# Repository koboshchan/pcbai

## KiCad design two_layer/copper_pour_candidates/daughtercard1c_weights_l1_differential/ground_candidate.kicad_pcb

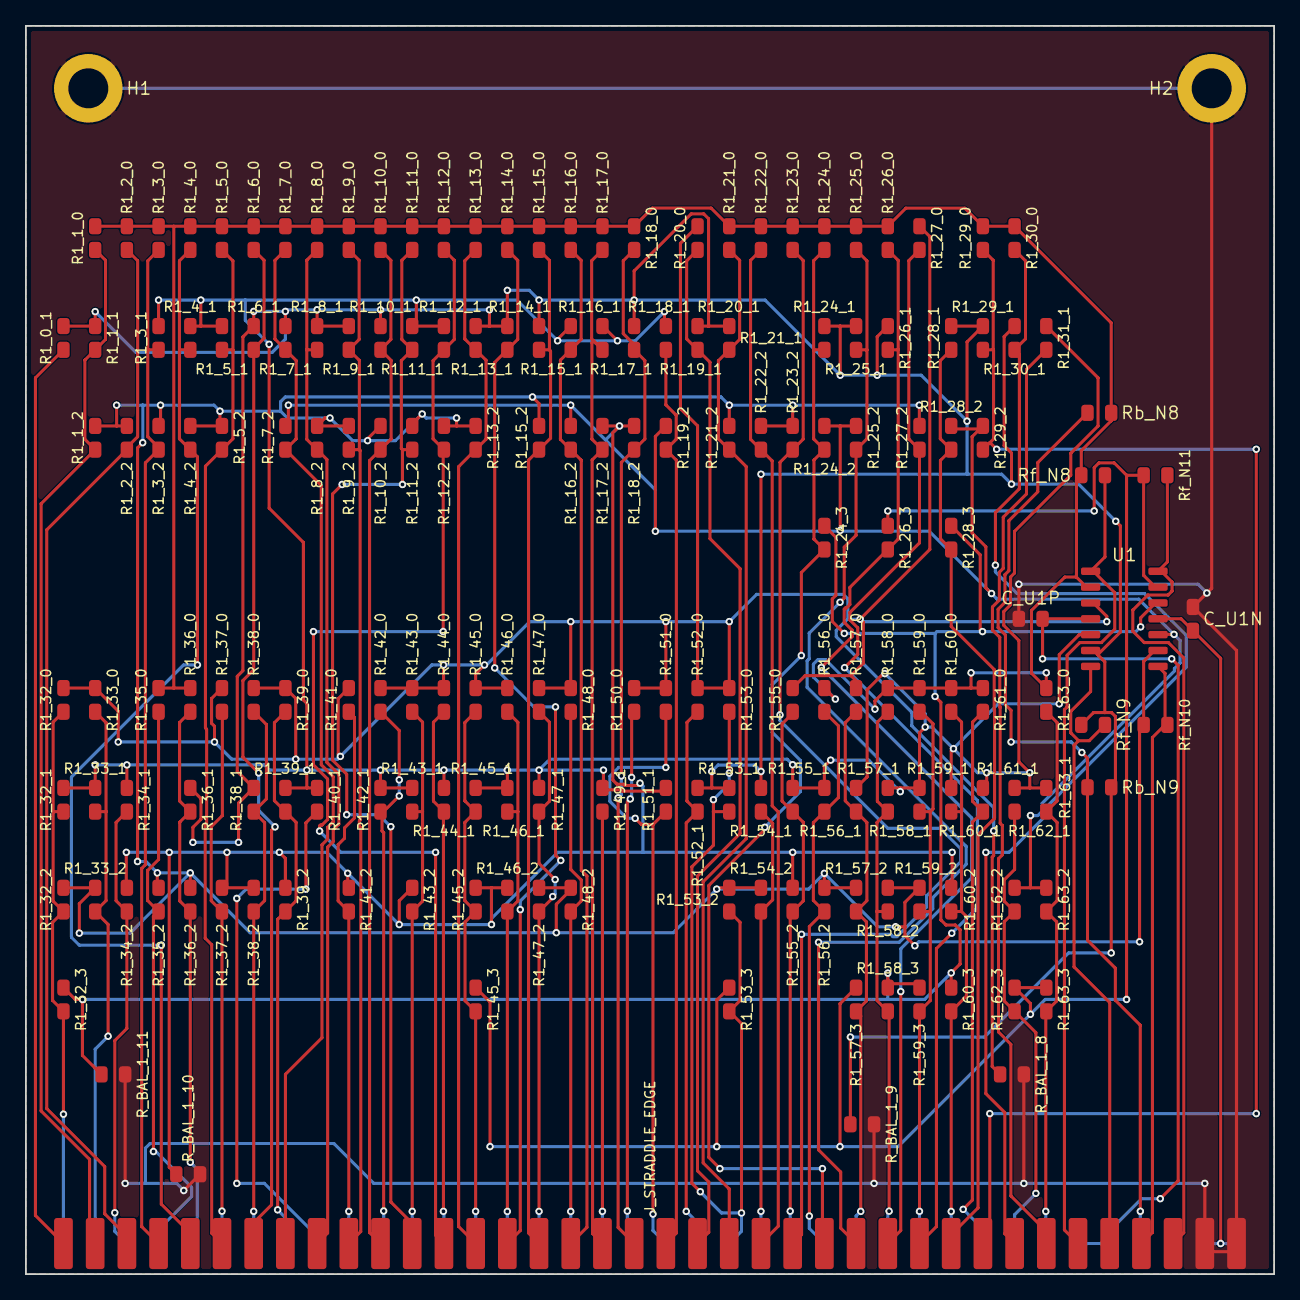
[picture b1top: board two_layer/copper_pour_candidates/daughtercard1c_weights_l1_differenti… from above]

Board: 2 copper layers, 100.0 x 100.0 mm, 187 parts (0 on the bottom side), 80 nets.

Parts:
C_U1N, C_U1P: 0.1uF; C_0805_2012Metric
H1, H2: MountingHole; MountingHole_3.2mm_M3_Pad
J_STRADDLE_EDGE: PinHeader_2x38_Straddle; PinHeader_2x38_Straddle_P2.54mm
R1_0_1: 51k; R_0805_2012Metric
R1_1_0, R1_4_0, R1_11_1, R1_13_1, R1_23_2, R1_28_3, R1_43_1, R1_45_0: 180k; R_0805_2012Metric
R1_1_1: 33k; R_0805_2012Metric
R1_1_2, R1_4_1: 43k; R_0805_2012Metric
R1_2_0, R1_22_2, R1_26_1, R1_28_2, R1_33_1, R1_37_0, R1_37_2, R1_39_2, R1_44_0, R1_44_1, R1_45_1, R1_46_1, R1_48_2, R1_49_1, R1_59_2: 270k; R_0805_2012Metric
R1_2_2, R1_3_1, R1_18_2, R1_56_0: 62k; R_0805_2012Metric
R1_3_0, R1_36_2: 1M; R_0805_2012Metric
R1_3_2, R1_18_0, R1_22_0: 120k; R_0805_2012Metric
R1_4_2, R1_14_1, R1_17_0, R1_18_1, R1_34_1, R1_63_1: 160k; R_0805_2012Metric
R1_5_0, R1_9_1, R1_11_0, R1_47_2, R1_59_0: 360k; R_0805_2012Metric
R1_5_1, R1_8_0, R1_19_2: 75k; R_0805_2012Metric
R1_5_2, R1_10_1, R1_21_1, R1_28_1, R1_39_0, R1_41_0, R1_45_3, R1_63_0: 240k; R_0805_2012Metric
R1_6_0, R1_12_2, R1_19_1, R1_33_2, R1_57_2: 330k; R_0805_2012Metric
R1_6_1, R1_11_2, R1_15_1, R1_16_0, R1_32_0, R1_56_1, R1_60_3, R1_62_1: 110k; R_0805_2012Metric
R1_7_0, R1_16_2, R1_17_2, R1_32_2: 47k; R_0805_2012Metric
R1_7_1, R1_8_2, R1_47_1: 39k; R_0805_2012Metric
R1_7_2: 27k; R_0805_2012Metric
R1_8_1, R1_10_2, R1_16_1, R1_32_1, R1_38_0: 91k; R_0805_2012Metric
R1_9_0, R1_52_0, R1_53_0, R1_53_2: 620k; R_0805_2012Metric
R1_9_2, R1_56_2: 100k; R_0805_2012Metric
R1_10_0, R1_13_0, R1_17_1, R1_50_0, R1_51_0, R1_58_1, R1_58_2: 220k; R_0805_2012Metric
R1_12_0, R1_33_0, R1_46_2: 430k; R_0805_2012Metric
R1_12_1, R1_42_1, R1_43_0, R1_53_3, R1_57_0, R1_59_3, R1_61_0: 300k; R_0805_2012Metric
R1_13_2, R1_26_0, R1_43_2, R1_47_0, R1_58_3, R1_63_3: 560k; R_0805_2012Metric
R1_14_0, R1_38_1, R1_38_2, R1_60_0: 510k; R_0805_2012Metric
R1_15_0, R1_40_1, R1_61_1: 68k; R_0805_2012Metric
R1_15_2: 82k; R_0805_2012Metric
R1_20_0, R1_25_0, R1_27_0, R1_42_0, R1_60_1: 470k; R_0805_2012Metric
R1_20_1, R1_35_0, R1_41_2, R1_59_1: 390k; R_0805_2012Metric
R1_21_0, R1_23_0, R1_24_1, R1_30_1, R1_39_1, R1_57_1: 130k; R_0805_2012Metric
R1_21_2, R1_32_3, R1_34_2: 910k; R_0805_2012Metric
R1_24_0, R1_30_0, R1_54_2, R1_62_2: 200k; R_0805_2012Metric
R1_24_2, R1_55_1: 56k; R_0805_2012Metric
R1_24_3, R1_25_2, R1_35_2, R1_36_0, R1_51_1, R1_52_1: 750k; R_0805_2012Metric
R1_25_1, R1_29_1, R1_46_0, R1_57_3, R1_62_3: 150k; R_0805_2012Metric
R1_26_3: 2.2M; R_0805_2012Metric
R1_27_2, R1_53_1, R1_54_1, R1_60_2: 820k; R_0805_2012Metric
R1_29_0, R1_55_0: 1.2M; R_0805_2012Metric
R1_29_2, R1_55_2: 1.3M; R_0805_2012Metric
R1_31_1: 3M; R_0805_2012Metric
R1_36_1, R1_48_0: 1.1M; R_0805_2012Metric
R1_45_2: 2M; R_0805_2012Metric
R1_58_0: 680k; R_0805_2012Metric
R1_63_2: 36k; R_0805_2012Metric
R_BAL_1_8: 8.66k; R_0805_2012Metric
R_BAL_1_9: 18.2k; R_0805_2012Metric
R_BAL_1_10: 35.7k; R_0805_2012Metric
R_BAL_1_11: 90.9k; R_0805_2012Metric
Rb_N8: 820k; R_0805_2012Metric
Rb_N9: 270k; R_0805_2012Metric
Rf_N8, Rf_N9, Rf_N10, Rf_N11: 100k; R_0805_2012Metric
U1: TL074; SOIC-14_3.9x8.7mm_P1.27mm

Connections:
+5V_REF: J_STRADDLE_EDGE.B35, Rb_N8.1, Rb_N9.1
+15V: C_U1P.2, J_STRADDLE_EDGE.B33, J_STRADDLE_EDGE.B34, U1.4
-15V: C_U1N.1, J_STRADDLE_EDGE.B37, J_STRADDLE_EDGE.B38, U1.11
GND: C_U1N.2, C_U1P.1, H1.1, H2.1, J_STRADDLE_EDGE.A37, J_STRADDLE_EDGE.A38, R_BAL_1_8.2, R_BAL_1_9.2, R_BAL_1_10.2, R_BAL_1_11.2
INV_N8: R1_1_0.2, R1_2_0.2, R1_3_0.2, R1_4_0.2, R1_5_0.2, R1_6_0.2, R1_7_0.2, R1_8_0.2, R1_9_0.2, R1_10_0.2, R1_11_0.2, R1_12_0.2, R1_13_0.2, R1_14_0.2, R1_15_0.2, R1_16_0.2, R1_17_0.2, R1_18_0.2, R1_21_0.2, R1_22_0.2, R1_23_0.2, R1_24_0.2, R1_25_0.2, R1_26_0.2, R1_29_0.2, R1_30_0.2, R1_35_0.2, R1_36_0.2, R1_56_0.2, R1_58_0.2, R1_59_0.2, R1_60_0.2, R1_61_0.2, R1_63_0.2, Rb_N8.2, Rf_N8.1, U1.2
INV_N9: R1_0_1.2, R1_1_1.2, R1_6_1.2, R1_7_1.2, R1_8_1.2, R1_9_1.2, R1_10_1.2, R1_13_1.2, R1_14_1.2, R1_15_1.2, R1_18_1.2, R1_20_1.2, R1_21_1.2, R1_24_1.2, R1_25_1.2, R1_26_1.2, R1_28_1.2, R1_29_1.2, R1_30_1.2, R1_36_1.2, R1_38_1.2, R1_52_1.2, R1_53_1.2, R1_54_1.2, R_BAL_1_9.1, Rb_N9.2, Rf_N9.1, U1.6
INV_N10: R1_1_2.2, R1_2_2.2, R1_3_2.2, R1_4_2.2, R1_5_2.2, R1_8_2.2, R1_9_2.2, R1_10_2.2, R1_11_2.2, R1_12_2.2, R1_13_2.2, R1_15_2.2, R1_21_2.2, R1_22_2.2, R1_23_2.2, R1_27_2.2, R1_32_2.2, R1_33_2.2, R1_35_2.2, R1_36_2.2, R1_47_2.2, R1_48_2.2, R1_53_2.2, R1_54_2.2, R1_56_2.2, R1_57_2.2, R1_58_2.2, R1_59_2.2, Rf_N10.1, U1.9
INV_N11: R1_26_3.2, R1_45_3.2, R1_53_3.2, R1_57_3.2, R1_62_3.2, R1_63_3.2, Rf_N11.1, U1.13
IN_0: J_STRADDLE_EDGE.A1, R1_0_1.1
IN_1: J_STRADDLE_EDGE.A2, R1_1_0.1, R1_1_1.1, R1_1_2.1
IN_2: J_STRADDLE_EDGE.A3, R1_2_0.1, R1_2_2.1
IN_3: J_STRADDLE_EDGE.A4, R1_3_0.1, R1_3_1.1, R1_3_2.1
IN_4: J_STRADDLE_EDGE.A5, R1_4_0.1, R1_4_1.1, R1_4_2.1
IN_5: J_STRADDLE_EDGE.A6, R1_5_0.1, R1_5_1.1, R1_5_2.1
IN_6: J_STRADDLE_EDGE.A7, R1_6_0.1, R1_6_1.1
IN_7: J_STRADDLE_EDGE.A8, R1_7_0.1, R1_7_1.1, R1_7_2.1
IN_8: J_STRADDLE_EDGE.A9, R1_8_0.1, R1_8_1.1, R1_8_2.1
IN_9: J_STRADDLE_EDGE.A10, R1_9_0.1, R1_9_1.1, R1_9_2.1
IN_10: J_STRADDLE_EDGE.A11, R1_10_0.1, R1_10_1.1, R1_10_2.1
IN_11: J_STRADDLE_EDGE.A12, R1_11_0.1, R1_11_1.1, R1_11_2.1
IN_12: J_STRADDLE_EDGE.A13, R1_12_0.1, R1_12_1.1, R1_12_2.1
IN_13: J_STRADDLE_EDGE.A14, R1_13_0.1, R1_13_1.1, R1_13_2.1
IN_14: J_STRADDLE_EDGE.A15, R1_14_0.1, R1_14_1.1
IN_15: J_STRADDLE_EDGE.A16, R1_15_0.1, R1_15_1.1, R1_15_2.1
IN_16: J_STRADDLE_EDGE.A17, R1_16_0.1, R1_16_1.1, R1_16_2.1
IN_17: J_STRADDLE_EDGE.A18, R1_17_0.1, R1_17_1.1, R1_17_2.1
IN_18: J_STRADDLE_EDGE.A19, R1_18_0.1, R1_18_1.1, R1_18_2.1
IN_19: J_STRADDLE_EDGE.A20, R1_19_1.1, R1_19_2.1
IN_20: J_STRADDLE_EDGE.A21, R1_20_0.1, R1_20_1.1
IN_21: J_STRADDLE_EDGE.A22, R1_21_0.1, R1_21_1.1, R1_21_2.1
IN_22: J_STRADDLE_EDGE.A23, R1_22_0.1, R1_22_2.1
IN_23: J_STRADDLE_EDGE.A24, R1_23_0.1, R1_23_2.1
IN_24: J_STRADDLE_EDGE.A25, R1_24_0.1, R1_24_1.1, R1_24_2.1, R1_24_3.1
IN_25: J_STRADDLE_EDGE.A26, R1_25_0.1, R1_25_1.1, R1_25_2.1
IN_26: J_STRADDLE_EDGE.A27, R1_26_0.1, R1_26_1.1, R1_26_3.1
IN_27: J_STRADDLE_EDGE.A28, R1_27_0.1, R1_27_2.1
IN_28: J_STRADDLE_EDGE.A29, R1_28_1.1, R1_28_2.1, R1_28_3.1
IN_29: J_STRADDLE_EDGE.A30, R1_29_0.1, R1_29_1.1, R1_29_2.1
IN_30: J_STRADDLE_EDGE.A31, R1_30_0.1, R1_30_1.1
IN_31: J_STRADDLE_EDGE.A32, R1_31_1.1
IN_32: J_STRADDLE_EDGE.B1, R1_32_0.1, R1_32_1.1, R1_32_2.1, R1_32_3.1
IN_33: J_STRADDLE_EDGE.B2, R1_33_0.1, R1_33_1.1, R1_33_2.1
IN_34: J_STRADDLE_EDGE.B3, R1_34_1.1, R1_34_2.1
IN_35: J_STRADDLE_EDGE.B4, R1_35_0.1, R1_35_2.1
IN_36: J_STRADDLE_EDGE.B5, R1_36_0.1, R1_36_1.1, R1_36_2.1
IN_37: J_STRADDLE_EDGE.B6, R1_37_0.1, R1_37_2.1
IN_38: J_STRADDLE_EDGE.B7, R1_38_0.1, R1_38_1.1, R1_38_2.1
IN_39: J_STRADDLE_EDGE.B8, R1_39_0.1, R1_39_1.1, R1_39_2.1
IN_40: J_STRADDLE_EDGE.B9, R1_40_1.1
IN_41: J_STRADDLE_EDGE.B10, R1_41_0.1, R1_41_2.1
IN_42: J_STRADDLE_EDGE.B11, R1_42_0.1, R1_42_1.1
IN_43: J_STRADDLE_EDGE.B12, R1_43_0.1, R1_43_1.1, R1_43_2.1
IN_44: J_STRADDLE_EDGE.B13, R1_44_0.1, R1_44_1.1
IN_45: J_STRADDLE_EDGE.B14, R1_45_0.1, R1_45_1.1, R1_45_2.1, R1_45_3.1
IN_46: J_STRADDLE_EDGE.B15, R1_46_0.1, R1_46_1.1, R1_46_2.1
IN_47: J_STRADDLE_EDGE.B16, R1_47_0.1, R1_47_1.1, R1_47_2.1
IN_48: J_STRADDLE_EDGE.B17, R1_48_0.1, R1_48_2.1
IN_49: J_STRADDLE_EDGE.B18, R1_49_1.1
IN_50: J_STRADDLE_EDGE.B19, R1_50_0.1
IN_51: J_STRADDLE_EDGE.B20, R1_51_0.1, R1_51_1.1
IN_52: J_STRADDLE_EDGE.B21, R1_52_0.1, R1_52_1.1
IN_53: J_STRADDLE_EDGE.B22, R1_53_0.1, R1_53_1.1, R1_53_2.1, R1_53_3.1
IN_54: J_STRADDLE_EDGE.B23, R1_54_1.1, R1_54_2.1
IN_55: J_STRADDLE_EDGE.B24, R1_55_0.1, R1_55_1.1, R1_55_2.1
IN_56: J_STRADDLE_EDGE.B25, R1_56_0.1, R1_56_1.1, R1_56_2.1
IN_57: J_STRADDLE_EDGE.B26, R1_57_0.1, R1_57_1.1, R1_57_2.1, R1_57_3.1
IN_58: J_STRADDLE_EDGE.B27, R1_58_0.1, R1_58_1.1, R1_58_2.1, R1_58_3.1
IN_59: J_STRADDLE_EDGE.B28, R1_59_0.1, R1_59_1.1, R1_59_2.1, R1_59_3.1
IN_60: J_STRADDLE_EDGE.B29, R1_60_0.1, R1_60_1.1, R1_60_2.1, R1_60_3.1
IN_61: J_STRADDLE_EDGE.B30, R1_61_0.1, R1_61_1.1
IN_62: J_STRADDLE_EDGE.B31, R1_62_1.1, R1_62_2.1, R1_62_3.1
IN_63: J_STRADDLE_EDGE.B32, R1_63_0.1, R1_63_1.1, R1_63_2.1, R1_63_3.1
POS_N8: R1_20_0.2, R1_27_0.2, R1_32_0.2, R1_33_0.2, R1_37_0.2, R1_38_0.2, R1_39_0.2, R1_41_0.2, R1_42_0.2, R1_43_0.2, R1_44_0.2, R1_45_0.2, R1_46_0.2, R1_47_0.2, R1_48_0.2, R1_50_0.2, R1_51_0.2, R1_52_0.2, R1_53_0.2, R1_55_0.2, R1_57_0.2, R_BAL_1_8.1, U1.3
POS_N9: R1_3_1.2, R1_4_1.2, R1_5_1.2, R1_11_1.2, R1_12_1.2, R1_16_1.2, R1_17_1.2, R1_19_1.2, R1_31_1.2, R1_32_1.2, R1_33_1.2, R1_34_1.2, R1_39_1.2, R1_40_1.2, R1_42_1.2, R1_43_1.2, R1_44_1.2, R1_45_1.2, R1_46_1.2, R1_47_1.2, R1_49_1.2, R1_51_1.2, R1_55_1.2, R1_56_1.2, R1_57_1.2, R1_58_1.2, R1_59_1.2, R1_60_1.2, R1_61_1.2, R1_62_1.2, R1_63_1.2, U1.5
POS_N10: R1_7_2.2, R1_16_2.2, R1_17_2.2, R1_18_2.2, R1_19_2.2, R1_24_2.2, R1_25_2.2, R1_28_2.2, R1_29_2.2, R1_34_2.2, R1_37_2.2, R1_38_2.2, R1_39_2.2, R1_41_2.2, R1_43_2.2, R1_45_2.2, R1_46_2.2, R1_55_2.2, R1_60_2.2, R1_62_2.2, R1_63_2.2, R_BAL_1_10.1, U1.10
POS_N11: R1_24_3.2, R1_28_3.2, R1_32_3.2, R1_58_3.2, R1_59_3.2, R1_60_3.2, R_BAL_1_11.1, U1.12
V_SUM_8: J_STRADDLE_EDGE.A33, Rf_N8.2, U1.1
V_SUM_9: J_STRADDLE_EDGE.A34, Rf_N9.2, U1.7
V_SUM_10: J_STRADDLE_EDGE.A35, Rf_N10.2, U1.8
V_SUM_11: J_STRADDLE_EDGE.A36, Rf_N11.2, U1.14

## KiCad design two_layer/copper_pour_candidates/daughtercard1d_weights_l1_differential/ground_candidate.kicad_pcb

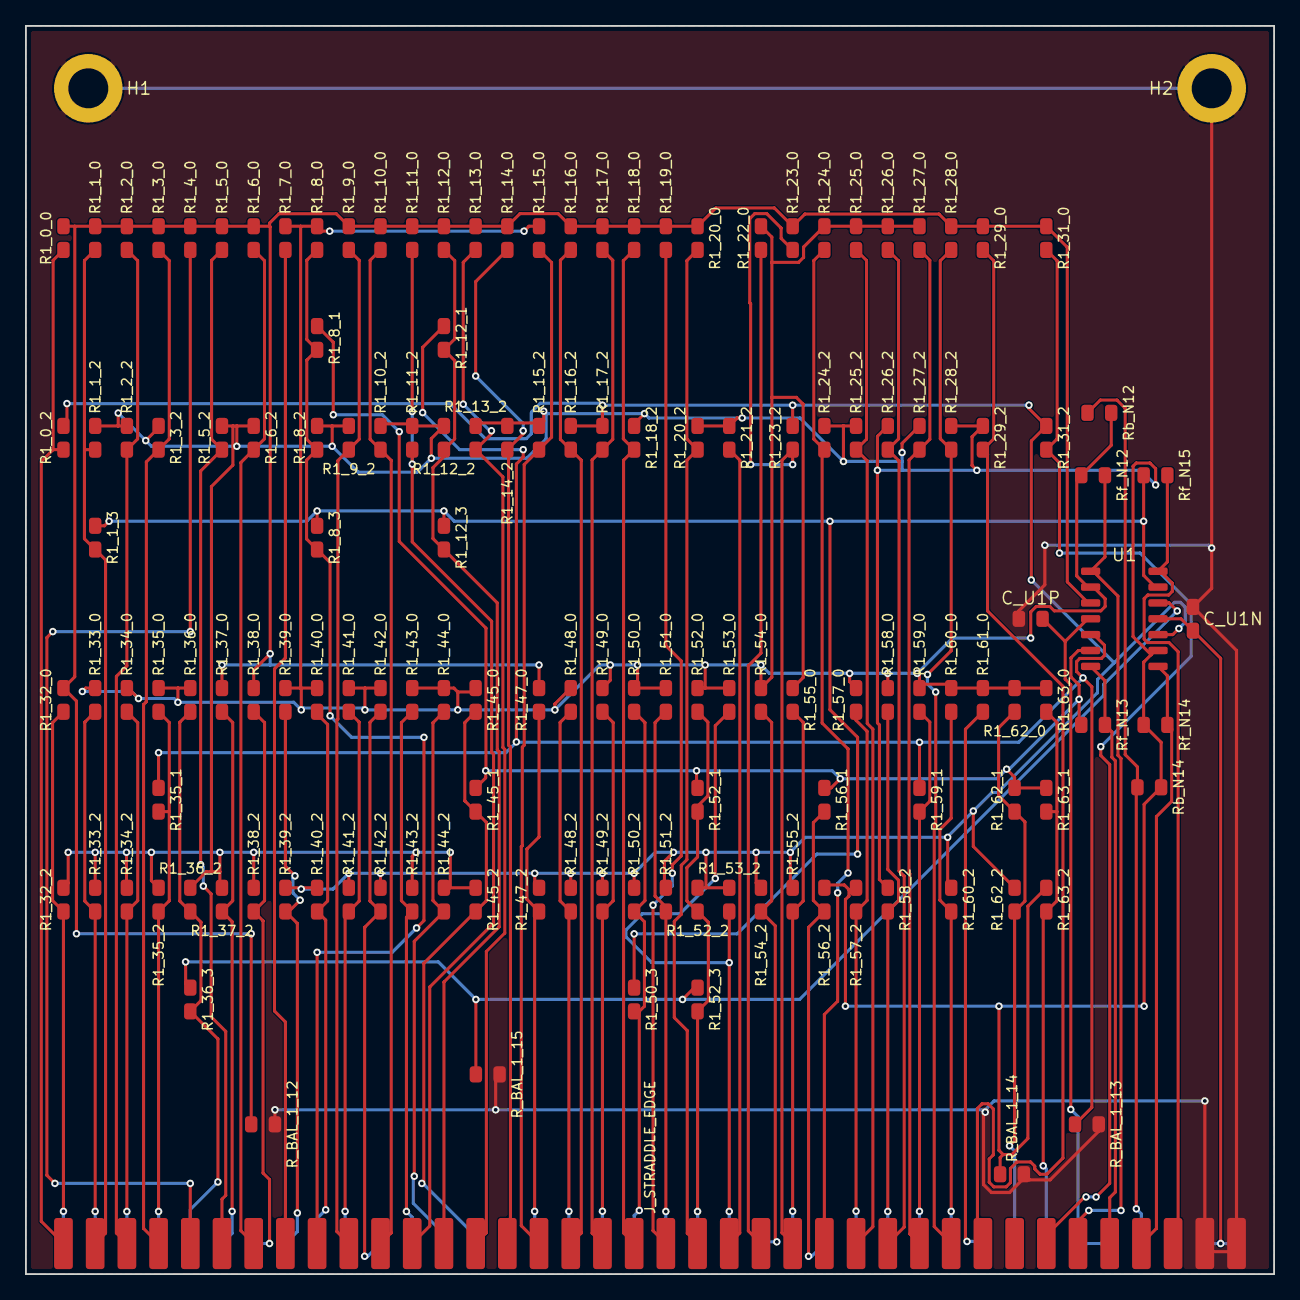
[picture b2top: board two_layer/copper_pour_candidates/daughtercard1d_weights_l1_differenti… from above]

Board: 2 copper layers, 100.0 x 100.0 mm, 147 parts (0 on the bottom side), 78 nets.

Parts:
C_U1N, C_U1P: 0.1uF; C_0805_2012Metric
H1, H2: MountingHole; MountingHole_3.2mm_M3_Pad
J_STRADDLE_EDGE: PinHeader_2x38_Straddle; PinHeader_2x38_Straddle_P2.54mm
R1_0_0: 43k; R_0805_2012Metric
R1_0_2, R1_31_2: 39k; R_0805_2012Metric
R1_1_0, R1_3_0, R1_5_2, R1_51_0, R1_56_1, R1_62_0, R1_62_1: 200k; R_0805_2012Metric
R1_1_2, R1_39_2: 91k; R_0805_2012Metric
R1_1_3, R1_12_3, R1_15_0, R1_17_2, R1_24_0, R1_34_0, R1_38_0: 220k; R_0805_2012Metric
R1_2_0, R1_13_0, R1_25_0, R1_63_1: 390k; R_0805_2012Metric
R1_2_2, R1_47_2, R1_55_0, R1_63_0: 100k; R_0805_2012Metric
R1_3_2, R1_24_2, R1_26_2, R1_48_2, R1_52_0, R1_59_0: 150k; R_0805_2012Metric
R1_4_0, R1_10_0, R1_14_2, R1_34_2, R1_50_0: 300k; R_0805_2012Metric
R1_5_0, R1_7_0, R1_9_2, R1_11_0, R1_13_2, R1_32_0, R1_37_2, R1_42_2, R1_49_0: 270k; R_0805_2012Metric
R1_6_0, R1_12_1, R1_18_2: 750k; R_0805_2012Metric
R1_6_2, R1_20_0: 110k; R_0805_2012Metric
R1_8_0, R1_25_2, R1_33_2, R1_36_2, R1_36_3, R1_41_2, R1_52_3, R1_57_0, R1_58_0, R1_61_0, R1_63_2: 160k; R_0805_2012Metric
R1_8_1, R1_28_2, R1_37_0, R1_40_0, R1_44_0, R1_45_0, R1_58_2: 430k; R_0805_2012Metric
R1_8_2, R1_56_2: 36k; R_0805_2012Metric
R1_8_3, R1_35_0, R1_41_0, R1_45_1, R1_59_1, R1_60_2: 180k; R_0805_2012Metric
R1_9_0, R1_43_2: 910k; R_0805_2012Metric
R1_10_2, R1_12_0, R1_26_0, R1_27_0, R1_35_2: 360k; R_0805_2012Metric
R1_11_2, R1_14_0, R1_16_0, R1_29_0, R1_33_0, R1_36_0, R1_52_1, R1_62_2: 330k; R_0805_2012Metric
R1_12_2: 1.1M; R_0805_2012Metric
R1_15_2, R1_47_0, R1_53_0: 120k; R_0805_2012Metric
R1_16_2, R1_52_2, R1_54_0: 75k; R_0805_2012Metric
R1_17_0, R1_23_0: 510k; R_0805_2012Metric
R1_18_0: 1M; R_0805_2012Metric
R1_19_0, R1_35_1, R1_39_0, R1_48_0: 130k; R_0805_2012Metric
R1_20_2: 820k; R_0805_2012Metric
R1_21_2: 2M; R_0805_2012Metric
R1_22_0: 1.5M; R_0805_2012Metric
R1_23_2: 51k; R_0805_2012Metric
R1_27_2, R1_45_2: 1.3M; R_0805_2012Metric
R1_28_0, R1_44_2: 560k; R_0805_2012Metric
R1_29_2, R1_32_2, R1_42_0: 470k; R_0805_2012Metric
R1_31_0, R1_38_2, R1_50_3, R1_55_2: 240k; R_0805_2012Metric
R1_40_2: 680k; R_0805_2012Metric
R1_43_0: 2.2M; R_0805_2012Metric
R1_49_2, R1_54_2: 68k; R_0805_2012Metric
R1_50_2, R1_57_2: 82k; R_0805_2012Metric
R1_51_2, R1_53_2: 62k; R_0805_2012Metric
R1_60_0: 1.2M; R_0805_2012Metric
R_BAL_1_12: 15.4k; R_0805_2012Metric
R_BAL_1_13: 52.3k; R_0805_2012Metric
R_BAL_1_14: 113k; R_0805_2012Metric
R_BAL_1_15: 61.9k; R_0805_2012Metric
Rb_N12: 750k; R_0805_2012Metric
Rb_N14: 200k; R_0805_2012Metric
Rf_N12, Rf_N13, Rf_N14, Rf_N15: 100k; R_0805_2012Metric
U1: TL074; SOIC-14_3.9x8.7mm_P1.27mm

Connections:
+5V_REF: J_STRADDLE_EDGE.B35, Rb_N12.1, Rb_N14.1
+15V: C_U1P.2, J_STRADDLE_EDGE.B33, J_STRADDLE_EDGE.B34, U1.4
-15V: C_U1N.1, J_STRADDLE_EDGE.B37, J_STRADDLE_EDGE.B38, U1.11
GND: C_U1N.2, C_U1P.1, H1.1, H2.1, J_STRADDLE_EDGE.A37, J_STRADDLE_EDGE.A38, R_BAL_1_12.2, R_BAL_1_13.2, R_BAL_1_14.2, R_BAL_1_15.2
INV_N12: R1_7_0.2, R1_8_0.2, R1_15_0.2, R1_22_0.2, R1_24_0.2, R1_25_0.2, R1_26_0.2, R1_27_0.2, R1_33_0.2, R1_34_0.2, R1_35_0.2, R1_36_0.2, R1_39_0.2, R1_40_0.2, R1_41_0.2, R1_42_0.2, R1_43_0.2, R1_44_0.2, R1_45_0.2, R1_48_0.2, R1_49_0.2, R1_50_0.2, R1_51_0.2, R1_52_0.2, R1_53_0.2, R1_54_0.2, R1_55_0.2, R1_57_0.2, R1_58_0.2, R1_59_0.2, R1_60_0.2, R1_61_0.2, R1_62_0.2, R1_63_0.2, Rb_N12.2, Rf_N12.1, U1.2
INV_N13: R1_8_1.2, R1_45_1.2, R1_52_1.2, R1_56_1.2, R1_62_1.2, R1_63_1.2, Rf_N13.1, U1.6
INV_N14: R1_1_2.2, R1_2_2.2, R1_3_2.2, R1_5_2.2, R1_6_2.2, R1_8_2.2, R1_9_2.2, R1_10_2.2, R1_11_2.2, R1_12_2.2, R1_13_2.2, R1_14_2.2, R1_15_2.2, R1_18_2.2, R1_20_2.2, R1_21_2.2, R1_24_2.2, R1_25_2.2, R1_26_2.2, R1_27_2.2, R1_28_2.2, R1_29_2.2, R1_32_2.2, R1_33_2.2, R1_34_2.2, R1_35_2.2, R1_36_2.2, R1_37_2.2, R1_38_2.2, R1_43_2.2, R1_44_2.2, R1_45_2.2, R1_56_2.2, R1_57_2.2, R1_58_2.2, R1_63_2.2, R_BAL_1_14.1, Rb_N14.2, Rf_N14.1, U1.9
INV_N15: R1_1_3.2, R1_8_3.2, R1_12_3.2, R1_50_3.2, Rf_N15.1, U1.13
IN_0: J_STRADDLE_EDGE.A1, R1_0_0.1, R1_0_2.1
IN_1: J_STRADDLE_EDGE.A2, R1_1_0.1, R1_1_2.1, R1_1_3.1
IN_2: J_STRADDLE_EDGE.A3, R1_2_0.1, R1_2_2.1
IN_3: J_STRADDLE_EDGE.A4, R1_3_0.1, R1_3_2.1
IN_4: J_STRADDLE_EDGE.A5, R1_4_0.1
IN_5: J_STRADDLE_EDGE.A6, R1_5_0.1, R1_5_2.1
IN_6: J_STRADDLE_EDGE.A7, R1_6_0.1, R1_6_2.1
IN_7: J_STRADDLE_EDGE.A8, R1_7_0.1
IN_8: J_STRADDLE_EDGE.A9, R1_8_0.1, R1_8_1.1, R1_8_2.1, R1_8_3.1
IN_9: J_STRADDLE_EDGE.A10, R1_9_0.1, R1_9_2.1
IN_10: J_STRADDLE_EDGE.A11, R1_10_0.1, R1_10_2.1
IN_11: J_STRADDLE_EDGE.A12, R1_11_0.1, R1_11_2.1
IN_12: J_STRADDLE_EDGE.A13, R1_12_0.1, R1_12_1.1, R1_12_2.1, R1_12_3.1
IN_13: J_STRADDLE_EDGE.A14, R1_13_0.1, R1_13_2.1
IN_14: J_STRADDLE_EDGE.A15, R1_14_0.1, R1_14_2.1
IN_15: J_STRADDLE_EDGE.A16, R1_15_0.1, R1_15_2.1
IN_16: J_STRADDLE_EDGE.A17, R1_16_0.1, R1_16_2.1
IN_17: J_STRADDLE_EDGE.A18, R1_17_0.1, R1_17_2.1
IN_18: J_STRADDLE_EDGE.A19, R1_18_0.1, R1_18_2.1
IN_19: J_STRADDLE_EDGE.A20, R1_19_0.1
IN_20: J_STRADDLE_EDGE.A21, R1_20_0.1, R1_20_2.1
IN_21: J_STRADDLE_EDGE.A22, R1_21_2.1
IN_22: J_STRADDLE_EDGE.A23, R1_22_0.1
IN_23: J_STRADDLE_EDGE.A24, R1_23_0.1, R1_23_2.1
IN_24: J_STRADDLE_EDGE.A25, R1_24_0.1, R1_24_2.1
IN_25: J_STRADDLE_EDGE.A26, R1_25_0.1, R1_25_2.1
IN_26: J_STRADDLE_EDGE.A27, R1_26_0.1, R1_26_2.1
IN_27: J_STRADDLE_EDGE.A28, R1_27_0.1, R1_27_2.1
IN_28: J_STRADDLE_EDGE.A29, R1_28_0.1, R1_28_2.1
IN_29: J_STRADDLE_EDGE.A30, R1_29_0.1, R1_29_2.1
IN_31: J_STRADDLE_EDGE.A32, R1_31_0.1, R1_31_2.1
IN_32: J_STRADDLE_EDGE.B1, R1_32_0.1, R1_32_2.1
IN_33: J_STRADDLE_EDGE.B2, R1_33_0.1, R1_33_2.1
IN_34: J_STRADDLE_EDGE.B3, R1_34_0.1, R1_34_2.1
IN_35: J_STRADDLE_EDGE.B4, R1_35_0.1, R1_35_1.1, R1_35_2.1
IN_36: J_STRADDLE_EDGE.B5, R1_36_0.1, R1_36_2.1, R1_36_3.1
IN_37: J_STRADDLE_EDGE.B6, R1_37_0.1, R1_37_2.1
IN_38: J_STRADDLE_EDGE.B7, R1_38_0.1, R1_38_2.1
IN_39: J_STRADDLE_EDGE.B8, R1_39_0.1, R1_39_2.1
IN_40: J_STRADDLE_EDGE.B9, R1_40_0.1, R1_40_2.1
IN_41: J_STRADDLE_EDGE.B10, R1_41_0.1, R1_41_2.1
IN_42: J_STRADDLE_EDGE.B11, R1_42_0.1, R1_42_2.1
IN_43: J_STRADDLE_EDGE.B12, R1_43_0.1, R1_43_2.1
IN_44: J_STRADDLE_EDGE.B13, R1_44_0.1, R1_44_2.1
IN_45: J_STRADDLE_EDGE.B14, R1_45_0.1, R1_45_1.1, R1_45_2.1
IN_47: J_STRADDLE_EDGE.B16, R1_47_0.1, R1_47_2.1
IN_48: J_STRADDLE_EDGE.B17, R1_48_0.1, R1_48_2.1
IN_49: J_STRADDLE_EDGE.B18, R1_49_0.1, R1_49_2.1
IN_50: J_STRADDLE_EDGE.B19, R1_50_0.1, R1_50_2.1, R1_50_3.1
IN_51: J_STRADDLE_EDGE.B20, R1_51_0.1, R1_51_2.1
IN_52: J_STRADDLE_EDGE.B21, R1_52_0.1, R1_52_1.1, R1_52_2.1, R1_52_3.1
IN_53: J_STRADDLE_EDGE.B22, R1_53_0.1, R1_53_2.1
IN_54: J_STRADDLE_EDGE.B23, R1_54_0.1, R1_54_2.1
IN_55: J_STRADDLE_EDGE.B24, R1_55_0.1, R1_55_2.1
IN_56: J_STRADDLE_EDGE.B25, R1_56_1.1, R1_56_2.1
IN_57: J_STRADDLE_EDGE.B26, R1_57_0.1, R1_57_2.1
IN_58: J_STRADDLE_EDGE.B27, R1_58_0.1, R1_58_2.1
IN_59: J_STRADDLE_EDGE.B28, R1_59_0.1, R1_59_1.1
IN_60: J_STRADDLE_EDGE.B29, R1_60_0.1, R1_60_2.1
IN_61: J_STRADDLE_EDGE.B30, R1_61_0.1
IN_62: J_STRADDLE_EDGE.B31, R1_62_0.1, R1_62_1.1, R1_62_2.1
IN_63: J_STRADDLE_EDGE.B32, R1_63_0.1, R1_63_1.1, R1_63_2.1
POS_N12: R1_0_0.2, R1_1_0.2, R1_2_0.2, R1_3_0.2, R1_4_0.2, R1_5_0.2, R1_6_0.2, R1_9_0.2, R1_10_0.2, R1_11_0.2, R1_12_0.2, R1_13_0.2, R1_14_0.2, R1_16_0.2, R1_17_0.2, R1_18_0.2, R1_19_0.2, R1_20_0.2, R1_23_0.2, R1_28_0.2, R1_29_0.2, R1_31_0.2, R1_32_0.2, R1_37_0.2, R1_38_0.2, R1_47_0.2, R_BAL_1_12.1, U1.3
POS_N13: R1_12_1.2, R1_35_1.2, R1_59_1.2, R_BAL_1_13.1, U1.5
POS_N14: R1_0_2.2, R1_16_2.2, R1_17_2.2, R1_23_2.2, R1_31_2.2, R1_39_2.2, R1_40_2.2, R1_41_2.2, R1_42_2.2, R1_47_2.2, R1_48_2.2, R1_49_2.2, R1_50_2.2, R1_51_2.2, R1_52_2.2, R1_53_2.2, R1_54_2.2, R1_55_2.2, R1_60_2.2, R1_62_2.2, U1.10
POS_N15: R1_36_3.2, R1_52_3.2, R_BAL_1_15.1, U1.12
V_SUM_12: J_STRADDLE_EDGE.A33, Rf_N12.2, U1.1
V_SUM_13: J_STRADDLE_EDGE.A34, Rf_N13.2, U1.7
V_SUM_14: J_STRADDLE_EDGE.A35, Rf_N14.2, U1.8
V_SUM_15: J_STRADDLE_EDGE.A36, Rf_N15.2, U1.14

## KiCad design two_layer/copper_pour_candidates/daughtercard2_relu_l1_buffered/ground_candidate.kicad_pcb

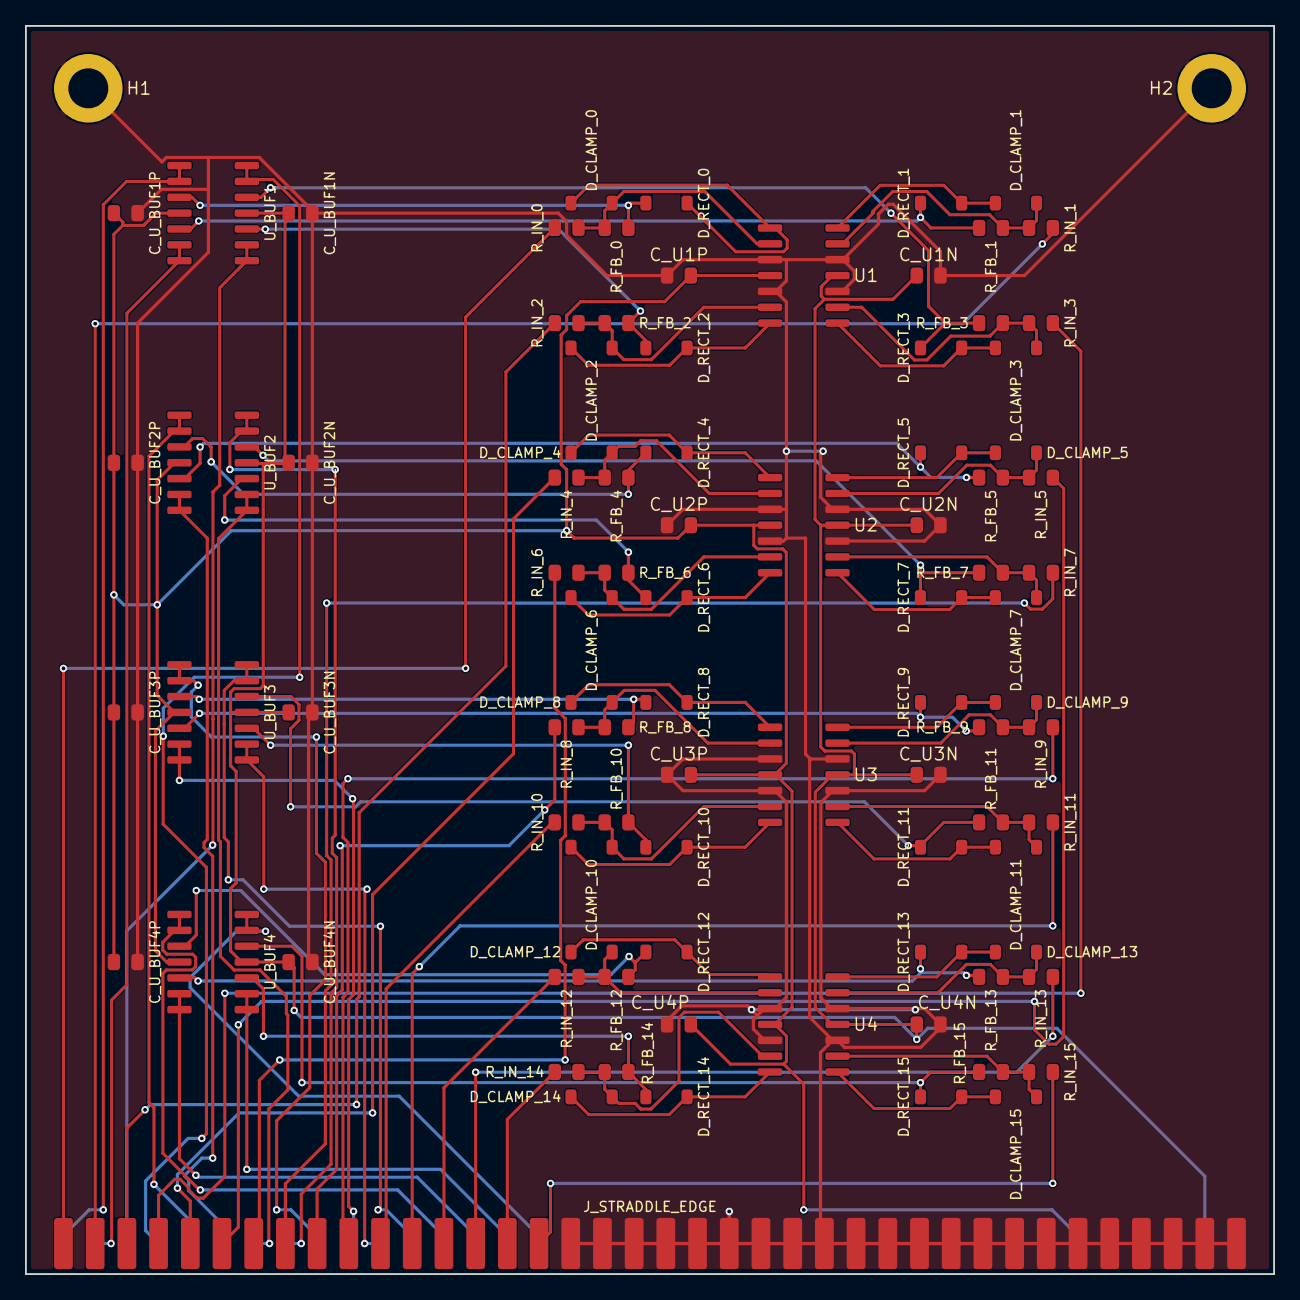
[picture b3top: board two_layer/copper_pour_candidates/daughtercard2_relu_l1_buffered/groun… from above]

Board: 2 copper layers, 100.0 x 100.0 mm, 91 parts (0 on the bottom side), 83 nets.

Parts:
C_U1N, C_U1P, C_U2N, C_U2P, C_U3N, C_U3P, C_U4N, C_U4P: 0.1uF; C_0805_2012Metric
C_U_BUF1N, C_U_BUF1P, C_U_BUF2N, C_U_BUF2P, C_U_BUF3N, C_U_BUF3P, C_U_BUF4N, C_U_BUF4P: 0.1uF; C_0805_2012Metric
D_CLAMP_0, D_CLAMP_1, D_CLAMP_2, D_CLAMP_3, D_CLAMP_4, D_CLAMP_5, D_CLAMP_6, D_CLAMP_7, D_CLAMP_8, D_CLAMP_9, D_CLAMP_10, D_CLAMP_11, D_CLAMP_12, D_CLAMP_13, D_CLAMP_14, D_CLAMP_15: 1N4148W; D_SOD-123
D_RECT_0, D_RECT_1, D_RECT_2, D_RECT_3, D_RECT_4, D_RECT_5, D_RECT_6, D_RECT_7, D_RECT_8, D_RECT_9, D_RECT_10, D_RECT_11, D_RECT_12, D_RECT_13, D_RECT_14, D_RECT_15: 1N4148W; D_SOD-123
H1, H2: MountingHole; MountingHole_3.2mm_M3_Pad
J_STRADDLE_EDGE: PinHeader_2x38_Straddle; PinHeader_2x38_Straddle_P2.54mm
R_FB_0, R_FB_1, R_FB_2, R_FB_3, R_FB_4, R_FB_5, R_FB_6, R_FB_7, R_FB_8, R_FB_9, R_FB_10, R_FB_11, R_FB_12, R_FB_13, R_FB_14, R_FB_15: 10k; R_0805_2012Metric
R_IN_0, R_IN_1, R_IN_2, R_IN_3, R_IN_4, R_IN_5, R_IN_6, R_IN_7, R_IN_8, R_IN_9, R_IN_10, R_IN_11, R_IN_12, R_IN_13, R_IN_14, R_IN_15: 10k; R_0805_2012Metric
U1, U2, U3, U4: TL074; SOIC-14_3.9x8.7mm_P1.27mm
U_BUF1, U_BUF2, U_BUF3, U_BUF4: TL074; SOIC-14_3.9x8.7mm_P1.27mm

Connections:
+15V: C_U1P.2, C_U2P.2, C_U3P.2, C_U4P.2, C_U_BUF1P.1, C_U_BUF2P.1, C_U_BUF3P.1, C_U_BUF4P.1, J_STRADDLE_EDGE.B33, J_STRADDLE_EDGE.B34, U1.4, U2.4, U3.4, U4.4, U_BUF1.4, U_BUF2.4, U_BUF3.4, U_BUF4.4
-15V: C_U1N.1, C_U2N.1, C_U3N.1, C_U4N.1, C_U_BUF1N.1, C_U_BUF2N.1, C_U_BUF3N.1, C_U_BUF4N.1, J_STRADDLE_EDGE.B37, J_STRADDLE_EDGE.B38, U1.11, U2.11, U3.11, U4.11, U_BUF1.11, U_BUF2.11, U_BUF3.11, U_BUF4.11
ACT_0: J_STRADDLE_EDGE.B1, U_BUF1.1, U_BUF1.2
ACT_1: J_STRADDLE_EDGE.B2, U_BUF1.6, U_BUF1.7
ACT_2: J_STRADDLE_EDGE.B3, U_BUF1.8, U_BUF1.9
ACT_3: J_STRADDLE_EDGE.B4, U_BUF1.13, U_BUF1.14
ACT_4: J_STRADDLE_EDGE.B5, U_BUF2.1, U_BUF2.2
ACT_5: J_STRADDLE_EDGE.B6, U_BUF2.6, U_BUF2.7
ACT_6: J_STRADDLE_EDGE.B7, U_BUF2.8, U_BUF2.9
ACT_7: J_STRADDLE_EDGE.B8, U_BUF2.13, U_BUF2.14
ACT_8: J_STRADDLE_EDGE.B9, U_BUF3.1, U_BUF3.2
ACT_9: J_STRADDLE_EDGE.B10, U_BUF3.6, U_BUF3.7
ACT_10: J_STRADDLE_EDGE.B11, U_BUF3.8, U_BUF3.9
ACT_11: J_STRADDLE_EDGE.B12, U_BUF3.13, U_BUF3.14
ACT_12: J_STRADDLE_EDGE.B13, U_BUF4.1, U_BUF4.2
ACT_13: J_STRADDLE_EDGE.B14, U_BUF4.6, U_BUF4.7
ACT_14: J_STRADDLE_EDGE.B15, U_BUF4.8, U_BUF4.9
ACT_15: J_STRADDLE_EDGE.B16, U_BUF4.13, U_BUF4.14
GND: C_U1N.2, C_U1P.1, C_U2N.2, C_U2P.1, C_U3N.2, C_U3P.1, C_U4N.2, C_U4P.1, C_U_BUF1N.2, C_U_BUF1P.2, C_U_BUF2N.2, C_U_BUF2P.2, C_U_BUF3N.2, C_U_BUF3P.2, C_U_BUF4N.2, C_U_BUF4P.2, H1.1, H2.1, J_STRADDLE_EDGE.A17, J_STRADDLE_EDGE.A18, J_STRADDLE_EDGE.A19, J_STRADDLE_EDGE.A20, J_STRADDLE_EDGE.A21, J_STRADDLE_EDGE.A22, J_STRADDLE_EDGE.A23, J_STRADDLE_EDGE.A24, J_STRADDLE_EDGE.A25, J_STRADDLE_EDGE.A26, J_STRADDLE_EDGE.A27, J_STRADDLE_EDGE.A28, J_STRADDLE_EDGE.A29, J_STRADDLE_EDGE.A30, J_STRADDLE_EDGE.A31, J_STRADDLE_EDGE.A32, J_STRADDLE_EDGE.A33, J_STRADDLE_EDGE.A34, J_STRADDLE_EDGE.A35, J_STRADDLE_EDGE.A36, J_STRADDLE_EDGE.A37, J_STRADDLE_EDGE.A38, J_STRADDLE_EDGE.B17, J_STRADDLE_EDGE.B18, J_STRADDLE_EDGE.B19, J_STRADDLE_EDGE.B20, J_STRADDLE_EDGE.B21, J_STRADDLE_EDGE.B22, J_STRADDLE_EDGE.B23, J_STRADDLE_EDGE.B24, J_STRADDLE_EDGE.B25, J_STRADDLE_EDGE.B26, J_STRADDLE_EDGE.B27, J_STRADDLE_EDGE.B28, J_STRADDLE_EDGE.B29, J_STRADDLE_EDGE.B30, J_STRADDLE_EDGE.B31, J_STRADDLE_EDGE.B32, U1.3, U1.5, U1.10, U1.12, U2.3, U2.5, U2.10, U2.12, U3.3, U3.5, U3.10, U3.12, U4.3, U4.5, U4.10, U4.12
INV_RELU_0: D_CLAMP_0.2, R_FB_0.1, R_IN_0.2, U1.2
INV_RELU_1: D_CLAMP_1.2, R_FB_1.2, R_IN_1.1, U1.13
INV_RELU_2: D_CLAMP_2.2, R_FB_2.1, R_IN_2.2, U1.6
INV_RELU_3: D_CLAMP_3.2, R_FB_3.2, R_IN_3.1, U1.9
INV_RELU_4: D_CLAMP_4.2, R_FB_4.1, R_IN_4.2, U2.2
INV_RELU_5: D_CLAMP_5.2, R_FB_5.2, R_IN_5.1, U2.13
INV_RELU_6: D_CLAMP_6.2, R_FB_6.1, R_IN_6.2, U2.6
INV_RELU_7: D_CLAMP_7.2, R_FB_7.2, R_IN_7.1, U2.9
INV_RELU_8: D_CLAMP_8.2, R_FB_8.1, R_IN_8.2, U3.2
INV_RELU_9: D_CLAMP_9.2, R_FB_9.2, R_IN_9.1, U3.13
INV_RELU_10: D_CLAMP_10.2, R_FB_10.1, R_IN_10.2, U3.6
INV_RELU_11: D_CLAMP_11.2, R_FB_11.2, R_IN_11.1, U3.9
INV_RELU_12: D_CLAMP_12.2, R_FB_12.1, R_IN_12.2, U4.2
INV_RELU_13: D_CLAMP_13.2, R_FB_13.2, R_IN_13.1, U4.13
INV_RELU_14: D_CLAMP_14.2, R_FB_14.1, R_IN_14.2, U4.6
INV_RELU_15: D_CLAMP_15.2, R_FB_15.2, R_IN_15.1, U4.9
OP_OUT_0: D_CLAMP_0.1, D_RECT_0.2, U1.1
OP_OUT_1: D_CLAMP_1.1, D_RECT_1.2, U1.14
OP_OUT_2: D_CLAMP_2.1, D_RECT_2.2, U1.7
OP_OUT_3: D_CLAMP_3.1, D_RECT_3.2, U1.8
OP_OUT_4: D_CLAMP_4.1, D_RECT_4.2, U2.1
OP_OUT_5: D_CLAMP_5.1, D_RECT_5.2, U2.14
OP_OUT_6: D_CLAMP_6.1, D_RECT_6.2, U2.7
OP_OUT_7: D_CLAMP_7.1, D_RECT_7.2, U2.8
OP_OUT_8: D_CLAMP_8.1, D_RECT_8.2, U3.1
OP_OUT_9: D_CLAMP_9.1, D_RECT_9.2, U3.14
OP_OUT_10: D_CLAMP_10.1, D_RECT_10.2, U3.7
OP_OUT_11: D_CLAMP_11.1, D_RECT_11.2, U3.8
OP_OUT_12: D_CLAMP_12.1, D_RECT_12.2, U4.1
OP_OUT_13: D_CLAMP_13.1, D_RECT_13.2, U4.14
OP_OUT_14: D_CLAMP_14.1, D_RECT_14.2, U4.7
OP_OUT_15: D_CLAMP_15.1, D_RECT_15.2, U4.8
RECT_0: D_RECT_0.1, R_FB_0.2, U_BUF1.3
RECT_1: D_RECT_1.1, R_FB_1.1, U_BUF1.5
RECT_2: D_RECT_2.1, R_FB_2.2, U_BUF1.10
RECT_3: D_RECT_3.1, R_FB_3.1, U_BUF1.12
RECT_4: D_RECT_4.1, R_FB_4.2, U_BUF2.3
RECT_5: D_RECT_5.1, R_FB_5.1, U_BUF2.5
RECT_6: D_RECT_6.1, R_FB_6.2, U_BUF2.10
RECT_7: D_RECT_7.1, R_FB_7.1, U_BUF2.12
RECT_8: D_RECT_8.1, R_FB_8.2, U_BUF3.3
RECT_9: D_RECT_9.1, R_FB_9.1, U_BUF3.5
RECT_10: D_RECT_10.1, R_FB_10.2, U_BUF3.10
RECT_11: D_RECT_11.1, R_FB_11.1, U_BUF3.12
RECT_12: D_RECT_12.1, R_FB_12.2, U_BUF4.3
RECT_13: D_RECT_13.1, R_FB_13.1, U_BUF4.5
RECT_14: D_RECT_14.1, R_FB_14.2, U_BUF4.10
RECT_15: D_RECT_15.1, R_FB_15.1, U_BUF4.12
V_SUM_0: J_STRADDLE_EDGE.A1, R_IN_0.1
V_SUM_1: J_STRADDLE_EDGE.A2, R_IN_1.2
V_SUM_2: J_STRADDLE_EDGE.A3, R_IN_2.1
V_SUM_3: J_STRADDLE_EDGE.A4, R_IN_3.2
V_SUM_4: J_STRADDLE_EDGE.A5, R_IN_4.1
V_SUM_5: J_STRADDLE_EDGE.A6, R_IN_5.2
V_SUM_6: J_STRADDLE_EDGE.A7, R_IN_6.1
V_SUM_7: J_STRADDLE_EDGE.A8, R_IN_7.2
V_SUM_8: J_STRADDLE_EDGE.A9, R_IN_8.1
V_SUM_9: J_STRADDLE_EDGE.A10, R_IN_9.2
V_SUM_10: J_STRADDLE_EDGE.A11, R_IN_10.1
V_SUM_11: J_STRADDLE_EDGE.A12, R_IN_11.2
V_SUM_12: J_STRADDLE_EDGE.A13, R_IN_12.1
V_SUM_13: J_STRADDLE_EDGE.A14, R_IN_13.2
V_SUM_14: J_STRADDLE_EDGE.A15, R_IN_14.1
V_SUM_15: J_STRADDLE_EDGE.A16, R_IN_15.2
